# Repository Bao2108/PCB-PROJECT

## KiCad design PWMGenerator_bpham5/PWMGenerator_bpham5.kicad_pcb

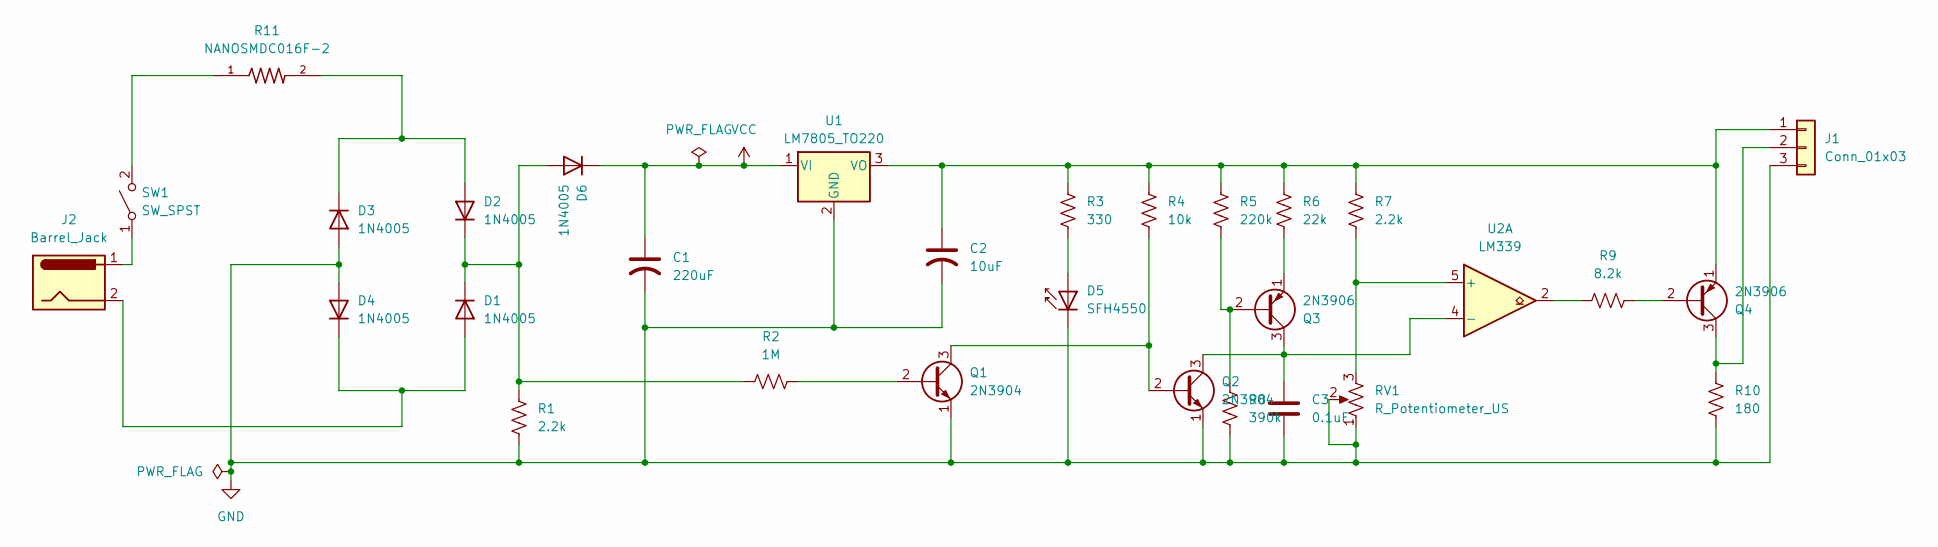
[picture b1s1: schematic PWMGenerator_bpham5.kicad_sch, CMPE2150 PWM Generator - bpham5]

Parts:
C1: 220uF; CP_Radial_D4.0mm_P2.00mm
C2: 10uF; CP_Radial_D4.0mm_P2.00mm
C3: 0.1uF; C_0805_2012Metric
D1, D2, D3, D4, D6: 1N4005; D_0805_2012Metric
D5: SFH4550; LED_D5.0mm_IRGrey
J1: Conn_01x03; PinHeader_1x03_P2.54mm_Vertical
J2: Barrel_Jack; BarrelJack_CUI_PJ-063AH_Horizontal
Q1, Q2: 2N3904; SOT-23
Q3, Q4: 2N3906; SOT-23
R1, R7: 2.2k; R_0805_2012Metric
R2: 1M; R_0805_2012Metric
R3: 330; R_0805_2012Metric
R4: 10k; R_0805_2012Metric
R5: 220k; R_0805_2012Metric
R6: 22k; R_0805_2012Metric
R8: 390k; R_0805_2012Metric
R9: 8.2k; R_0805_2012Metric
R10: 180; R_0805_2012Metric
R11: NANOSMDC016F-2; RESC3115X65N
RV1: R_Potentiometer_US; Potentiometer_ACP_CA9-V10_Vertical_Hole
SW1: SW_SPST; SW_DIP_SPSTx01_Slide_6.7x4.1mm_W6.73mm_P2.54mm_LowProfile_J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
U1: LM7805_TO220; TO-220-3_Horizontal_TabDown
U2: LM339; SOIC-14_3.9x8.7mm_P1.27mm

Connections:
GND: C1.2, C2.2, C3.2, D3.2 (A), D4.2 (A), D5.1 (K), J1.3, Q1.1 (E), Q2.1 (E), R1.1, R8.2, R10.1, RV1.1, RV1.2, U1.2 (GND)
unnamed: D1.2 (A), D4.1 (K), J2.2
unnamed: D1.1 (K), D2.1 (K), D6.2 (A), R1.2, R2.1
unnamed: D2.2 (A), D3.1 (K), R11.2
unnamed: D5.2 (A), R3.2
unnamed: C1.1, D6.1 (K), U1.1 (VI)
unnamed: C2.1, J1.1, Q4.1 (E), R3.1, R4.1, R5.1, R6.1, R7.1, U1.3 (VO)
unnamed: J1.2, Q4.3 (C), R10.2
unnamed: Q1.2 (B), R2.2
unnamed: Q1.3 (C), Q2.2 (B), R4.2
unnamed: C3.1, Q2.3 (C), Q3.3 (C), U2.4 (-)
unnamed: Q3.2 (B), R5.2, R8.1
unnamed: Q3.1 (E), R6.2
unnamed: Q4.2 (B), R9.2
unnamed: R9.1, U2.2
unnamed: J2.1, SW1.1 (A)
unnamed: R11.1, SW1.2 (B)
unnamed: R7.2, RV1.3, U2.5 (+)

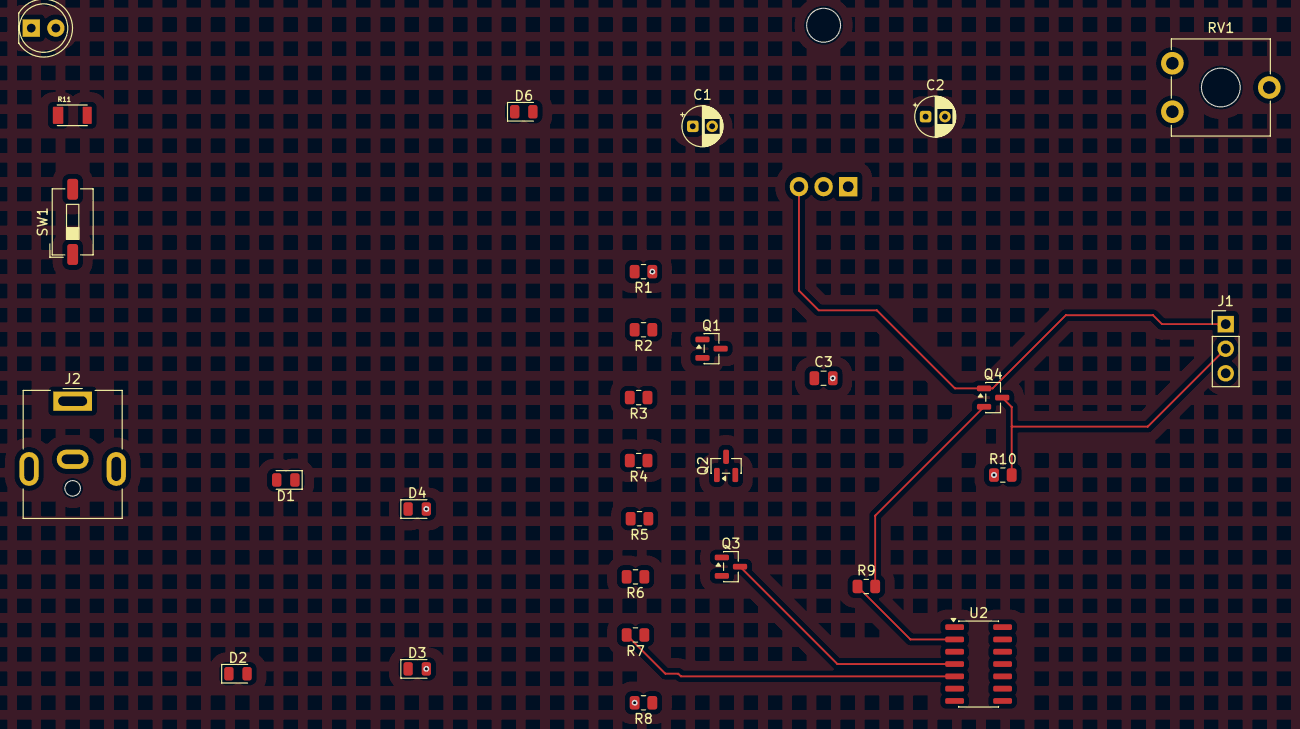
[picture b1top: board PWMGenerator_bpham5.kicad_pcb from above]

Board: 2 copper layers, 30 parts (1 on the bottom side), 18 nets.

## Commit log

2025-12-09 PCB PART A
2025-12-12 part b in progress, just added new lib
2025-12-12 partbcompleted
2025-12-12 part b completed
2025-12-12 part b fixed
2025-12-12 PROJECT C STARTED
2025-12-16 PCB IN PROGRESS
2025-12-16 PCB ALMOST COMPLETED
